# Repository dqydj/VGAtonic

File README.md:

VGAtonic
========

4 MBit Video Card supporting up to 640x480 resolution and 8 bit color depth over SPI.  Outputs to any standard VGA Monitor.

**What it is:**

VGAtonic is a video card for adding graphics output to computers, microcontrollers, and devices with SPI output.  It can generally support 5v, 3.3v and 2.5v SPI without level conversion, and can accept SPI of up to 60 MHz (or higher), giving 24.4 FPS as a worst case top speed for it's highest resolution and color depth.  It is also an entry to the [2015](https://hackaday.io/project/6309-vga-graphics-card-vgatonic) and [2014](https://hackaday.io/project/1943-vgatonic) Hackaday Prize competitions.

It additionally has hardware supported accelerations for various things, meaning that slower SPI links can still have useful display output:

 - 640x480 resolution  
 - 320x240 resolution
 - 160x120 resolution
 - 80x60 resolution
 - 8 bit color (256 colors)
 - 4 bit color (16 colors)
 - 2 bit color (4 colors)
 - 1 bit color (black & white)

Last, it also *accelerates screen positioning*, so the entire framebuffer need not be updated for a single refresh (allowing, for example, a menubar at the bottom of the screen to be updated at the full 60 Hz possible in the 640x480 resolution mode).

Importantly, all of these accelerations stack, so if you have a 4 MHz link, you can choose to target, say, 160x120x4 bits for 52 FPS worst case.

**How it's made:**

See the entire parts list in [this Hackaday Prize post](https://hackaday.io/project/6309-spi-and-ttl-serial-vga-graphics-card-vgatonic/log/21984-updated-bill-of-materials).  As part of the project, to keep it *interesting* (and keep costs down) I used modestly spec'd parts - a 144 Macrocell Xilinx XC95144XL CPLD instead of a large FPGA, and an 8 bit 128-Bytes of RAM Atmel ATTiny 2313a Microcontroller instead of one of the larger Atmel parts or something 32-bit (it's not even the largest part in its footprint).  Additionally, the pixel clock is provided by Linear Technology's LTC6903, allowing it to be changed on the fly (and, undoubtedly, tuned for specific monitors) by the microcontroller.  

You can find the schematics in the Rev A directory..

As for the software:

 - KiCad for the layout and Schematic
 - VHDL on Xilinx's ISE Webpack for the CPLD
 - C/C++ for any Microcontroller and Computer glue
 - C for the kernel code for the VGATonic Linux framebuffer drivers
 - Python where necessary

**How it's licensed:**

MIT (Hardware, Firmware, Python Examples, Arduino Code)  

GPL (Linux Framebuffer Drivers, Linux Userspace Code)  

LGPL (Changes to Arduino-Tiny Core)

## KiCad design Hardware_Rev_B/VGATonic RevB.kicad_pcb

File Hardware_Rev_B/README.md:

**NOTE:  This is the current version that should be built.  It has the NTSC pins and almost the same number of GPIOs broken out as Rev A on the optional unpopulated header on the back.**

**For VGA, there is no contest - build Rev B.  You will get more serial speeds, better ground isolation, shielding on the SPI signals, and... LEDs!**

By default, you should try the REGULAR firmware, not the WIDESCREEN firmware.  640x480 at 60Hz is industry standard, so that's the fallback (and it allows 320x240, 160x120 and 80x60 resolutions too for your slower parts or when you want to drive VGATonic over serial).  Once your board is working, the WIDESCREEN firmware is *much* nicer, but it only offers 848x480 and 424x240 resolutions.  It is only tested on rev B, but it likely works on rev A - just be careful.  Note, too, that the TERMINAL EMULATOR only works with the REGULAR firmware, it isn't yet updated for WIDESCREEN.

In this directory you'll find the design documentation for VGAtonic's second design, which we're naming v1.25 or "Rev B".  It is 39% smaller than the first version and contains 54 components (counting the headers and a single component each).

Returning are the Xilinx XC95144 CPLD, the ISSI IS61LV5128AL Memory, and the Linear LTC6903.

We've switched the Atmel 2313a up with the Atmel ATTiny 4313 (it's pin compatible), and clocked it with a 7.3728 MHz crystal which gives us magic frequencies to support lots of new serial speeds.  An external clock also saves us the optional calibration step in programming, which could be a bit of a hassle - now we'll have just two steps for the microcontroller, burning EEPROM then programming the rest.

Oh, we also added LEDs!  That, of course, is the best new feature.

License: MIT (see root directory)

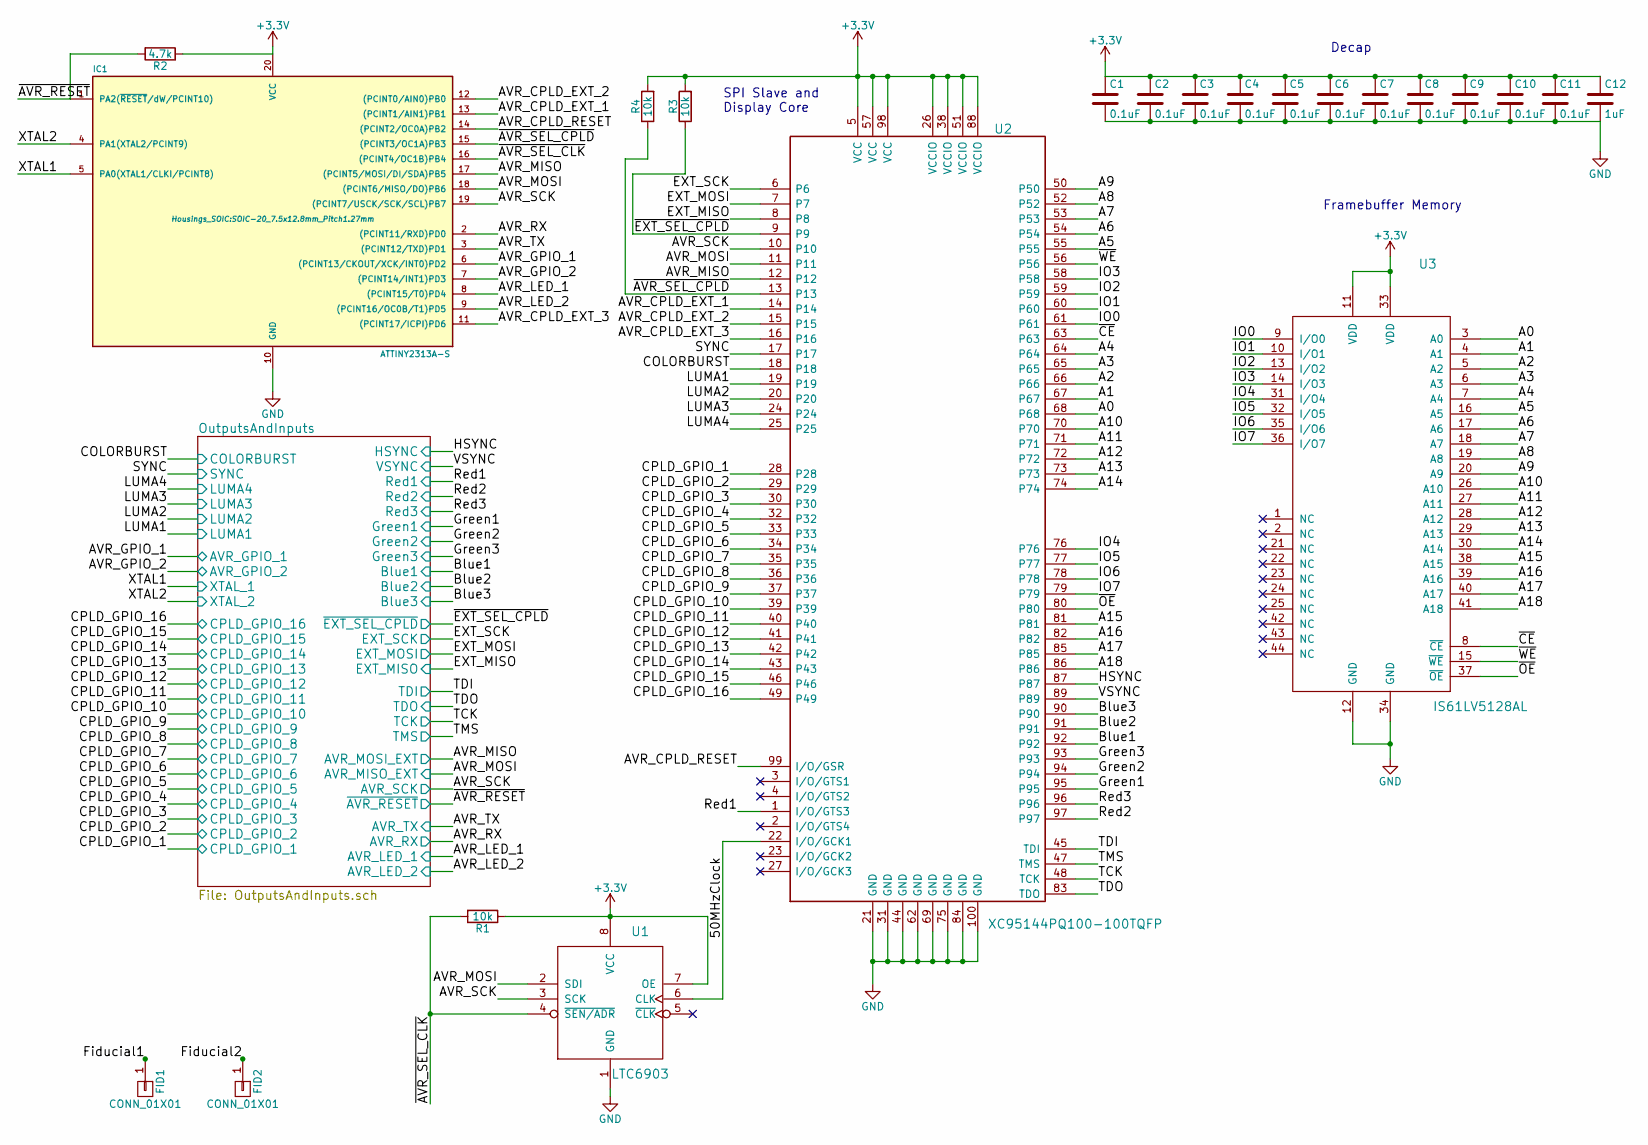
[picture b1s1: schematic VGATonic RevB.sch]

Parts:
C1, C2, C3, C4, C5, C6, C7, C8, C9, C10, C11: 0.1uF; C_0603
C12: 1uF; C_0603
FID1, FID2: CONN_01X01; Fiducial_1mm_Dia_2.54mm_Outer_CopperTop
IC1: ATTINY2313A-S; SOIC-20_7.5x12.8mm_Pitch1.27mm
R1, R3, R4: 10k; R_0805
R2: 4.7k; R_0805
U1: LTC6903; MSOP-8_3x3mm_Pitch0.65mm
U2: XC95144PQ100-100TQFP; TQFP-100_14x14mm_Pitch0.5mm
U3: IS61LV5128AL; tsop2-44

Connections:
+3V3: C1.1, C2.1, C3.1, C4.1, C5.1, C6.1, C7.1, C8.1, C9.1, C10.1, C11.1, C12.1, IC1.20 (VCC), R1.1, R2.1, R3.2, R4.2, U1.7 (OE), U1.8 (VCC), U2.5 (VCC), U2.26 (VCCIO), U2.38 (VCCIO), U2.51 (VCCIO), U2.57 (VCC), U2.88 (VCCIO), U2.98 (VCC), U3.11 (VDD), U3.33 (VDD); also elsewhere on the board
/50MHzClock: U1.6 (CLK), U2.22 (I/O/GCK1)
/A0: U2.68, U3.3 (A0)
/A1: U2.67, U3.4 (A1)
/A2: U2.66, U3.5 (A2)
/A3: U2.65, U3.6 (A3)
/A4: U2.64, U3.7 (A4)
/A5: U2.55, U3.16 (A5)
/A6: U2.54, U3.17 (A6)
/A7: U2.53, U3.18 (A7)
/A8: U2.52, U3.19 (A8)
/A9: U2.50, U3.20 (A9)
/A10: U2.70, U3.26 (A10)
/A11: U2.71, U3.27 (A11)
/A12: U2.72, U3.28 (A12)
/A13: U2.73, U3.29 (A13)
/A14: U2.74, U3.30 (A14)
/A15: U2.81, U3.38 (A15)
/A16: U2.82, U3.39 (A16)
/A17: U2.85, U3.40 (A17)
/A18: U2.86, U3.41 (A18)
/AVR_CPLD_EXT_1: IC1.13 ((PCINT1/AIN1)PB1), U2.14
/AVR_CPLD_EXT_2: IC1.12 ((PCINT0/AIN0)PB0), U2.15
/AVR_CPLD_EXT_3: IC1.11 ((PCINT17/ICPI)PD6), U2.16
/AVR_CPLD_RESET: IC1.14 ((PCINT2/OC0A)PB2), U2.99 (I/O/GSR)
/IO0: U2.61, U3.9 (I/O0)
/IO1: U2.60, U3.10 (I/O1)
/IO2: U2.59, U3.13 (I/O2)
/IO3: U2.58, U3.14 (I/O3)
/IO4: U2.76, U3.31 (I/O4)
/IO5: U2.77, U3.32 (I/O5)
/IO6: U2.78, U3.35 (I/O6)
/IO7: U2.79, U3.36 (I/O7)
/OutputsAndInputs/AVR_GPIO_1: IC1.6 ((PCINT13/CKOUT/XCK/INT0)PD2); also elsewhere on the board
/OutputsAndInputs/AVR_GPIO_2: IC1.7 ((PCINT14/INT1)PD3); also elsewhere on the board
/OutputsAndInputs/AVR_LED_1: IC1.8 ((PCINT15/T0)PD4); also elsewhere on the board
/OutputsAndInputs/AVR_LED_2: IC1.9 ((PCINT16/OC0B/T1)PD5); also elsewhere on the board
/OutputsAndInputs/AVR_MISO_EXT: IC1.18 ((PCINT6/MISO/DO)PB6), U1.2 (SDI), U2.11; also elsewhere on the board
/OutputsAndInputs/AVR_MOSI_EXT: IC1.17 ((PCINT5/MOSI/DI/SDA)PB5), U2.12; also elsewhere on the board
/OutputsAndInputs/AVR_RX: IC1.2 ((PCINT11/RXD)PD0); also elsewhere on the board
/OutputsAndInputs/AVR_SCK: IC1.19 ((PCINT7/USCK/SCK/SCL)PB7), U1.3 (SCK), U2.10; also elsewhere on the board
/OutputsAndInputs/AVR_TX: IC1.3 ((PCINT12/TXD)PD1); also elsewhere on the board
/OutputsAndInputs/Blue1: U2.92; also elsewhere on the board
/OutputsAndInputs/Blue2: U2.91; also elsewhere on the board
/OutputsAndInputs/Blue3: U2.90; also elsewhere on the board
/OutputsAndInputs/COLORBURST: U2.18; also elsewhere on the board
/OutputsAndInputs/CPLD_GPIO_1: U2.28; also elsewhere on the board
/OutputsAndInputs/CPLD_GPIO_2: U2.29; also elsewhere on the board
/OutputsAndInputs/CPLD_GPIO_3: U2.30; also elsewhere on the board
/OutputsAndInputs/CPLD_GPIO_4: U2.32; also elsewhere on the board
/OutputsAndInputs/CPLD_GPIO_5: U2.33; also elsewhere on the board
/OutputsAndInputs/CPLD_GPIO_6: U2.34; also elsewhere on the board
/OutputsAndInputs/CPLD_GPIO_7: U2.35; also elsewhere on the board
/OutputsAndInputs/CPLD_GPIO_8: U2.36; also elsewhere on the board
/OutputsAndInputs/CPLD_GPIO_9: U2.37; also elsewhere on the board
/OutputsAndInputs/CPLD_GPIO_10: U2.39; also elsewhere on the board
/OutputsAndInputs/CPLD_GPIO_11: U2.40; also elsewhere on the board
/OutputsAndInputs/CPLD_GPIO_12: U2.41; also elsewhere on the board
/OutputsAndInputs/CPLD_GPIO_13: U2.42; also elsewhere on the board
/OutputsAndInputs/CPLD_GPIO_14: U2.43; also elsewhere on the board
/OutputsAndInputs/CPLD_GPIO_15: U2.46; also elsewhere on the board
/OutputsAndInputs/CPLD_GPIO_16: U2.49; also elsewhere on the board
/OutputsAndInputs/EXT_MISO: U2.8; also elsewhere on the board
/OutputsAndInputs/EXT_MOSI: U2.7; also elsewhere on the board
/OutputsAndInputs/EXT_SCK: U2.6; also elsewhere on the board
/OutputsAndInputs/Green1: U2.95; also elsewhere on the board
/OutputsAndInputs/Green2: U2.94; also elsewhere on the board
/OutputsAndInputs/Green3: U2.93; also elsewhere on the board
/OutputsAndInputs/HSYNC: U2.87; also elsewhere on the board
/OutputsAndInputs/LUMA1: U2.19; also elsewhere on the board
/OutputsAndInputs/LUMA2: U2.20; also elsewhere on the board
/OutputsAndInputs/LUMA3: U2.24; also elsewhere on the board
/OutputsAndInputs/LUMA4: U2.25; also elsewhere on the board
/OutputsAndInputs/Red1: U2.1 (I/O/GTS3); also elsewhere on the board
/OutputsAndInputs/Red2: U2.97; also elsewhere on the board
/OutputsAndInputs/Red3: U2.96; also elsewhere on the board
/OutputsAndInputs/SYNC: U2.17; also elsewhere on the board
/OutputsAndInputs/TCK: U2.48 (TCK); also elsewhere on the board
/OutputsAndInputs/TDI: U2.45 (TDI); also elsewhere on the board
/OutputsAndInputs/TDO: U2.83 (TDO); also elsewhere on the board
/OutputsAndInputs/TMS: U2.47 (TMS); also elsewhere on the board
/OutputsAndInputs/VSYNC: U2.89; also elsewhere on the board
/OutputsAndInputs/XTAL_1: IC1.5 (PA0(XTAL1/CLKI/PCINT8)); also elsewhere on the board
/OutputsAndInputs/XTAL_2: IC1.4 (PA1(XTAL2/PCINT9)); also elsewhere on the board
/OutputsAndInputs/~AVR_RESET: IC1.1 (PA2(~RESET~/dW/PCINT10)), R2.2; also elsewhere on the board
/OutputsAndInputs/~EXT_SEL_CPLD: R3.1, U2.9; also elsewhere on the board
/~AVR_SEL_CLK: IC1.16 ((PCINT4/OC1B)PB4), R1.2, U1.4 (~SEN/ADR)
/~AVR_SEL_CPLD: IC1.15 ((PCINT3/OC1A)PB3), R4.1, U2.13
/~CE: U2.63, U3.8 (~CE)
/~OE: U2.80, U3.37 (~OE)
/~WE: U2.56, U3.15 (~WE)
GND: C1.2, C2.2, C3.2, C4.2, C5.2, C6.2, C7.2, C8.2, C9.2, C10.2, C11.2, C12.2, IC1.10 (GND), U1.1 (GND), U2.21 (GND), U2.31 (GND), U2.44 (GND), U2.62 (GND), U2.69 (GND), U2.75 (GND), U2.84 (GND), U2.100 (GND), U3.12 (GND), U3.34 (GND); also elsewhere on the board

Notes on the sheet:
Decap
Framebuffer Memory
SPI Slave and Display Core

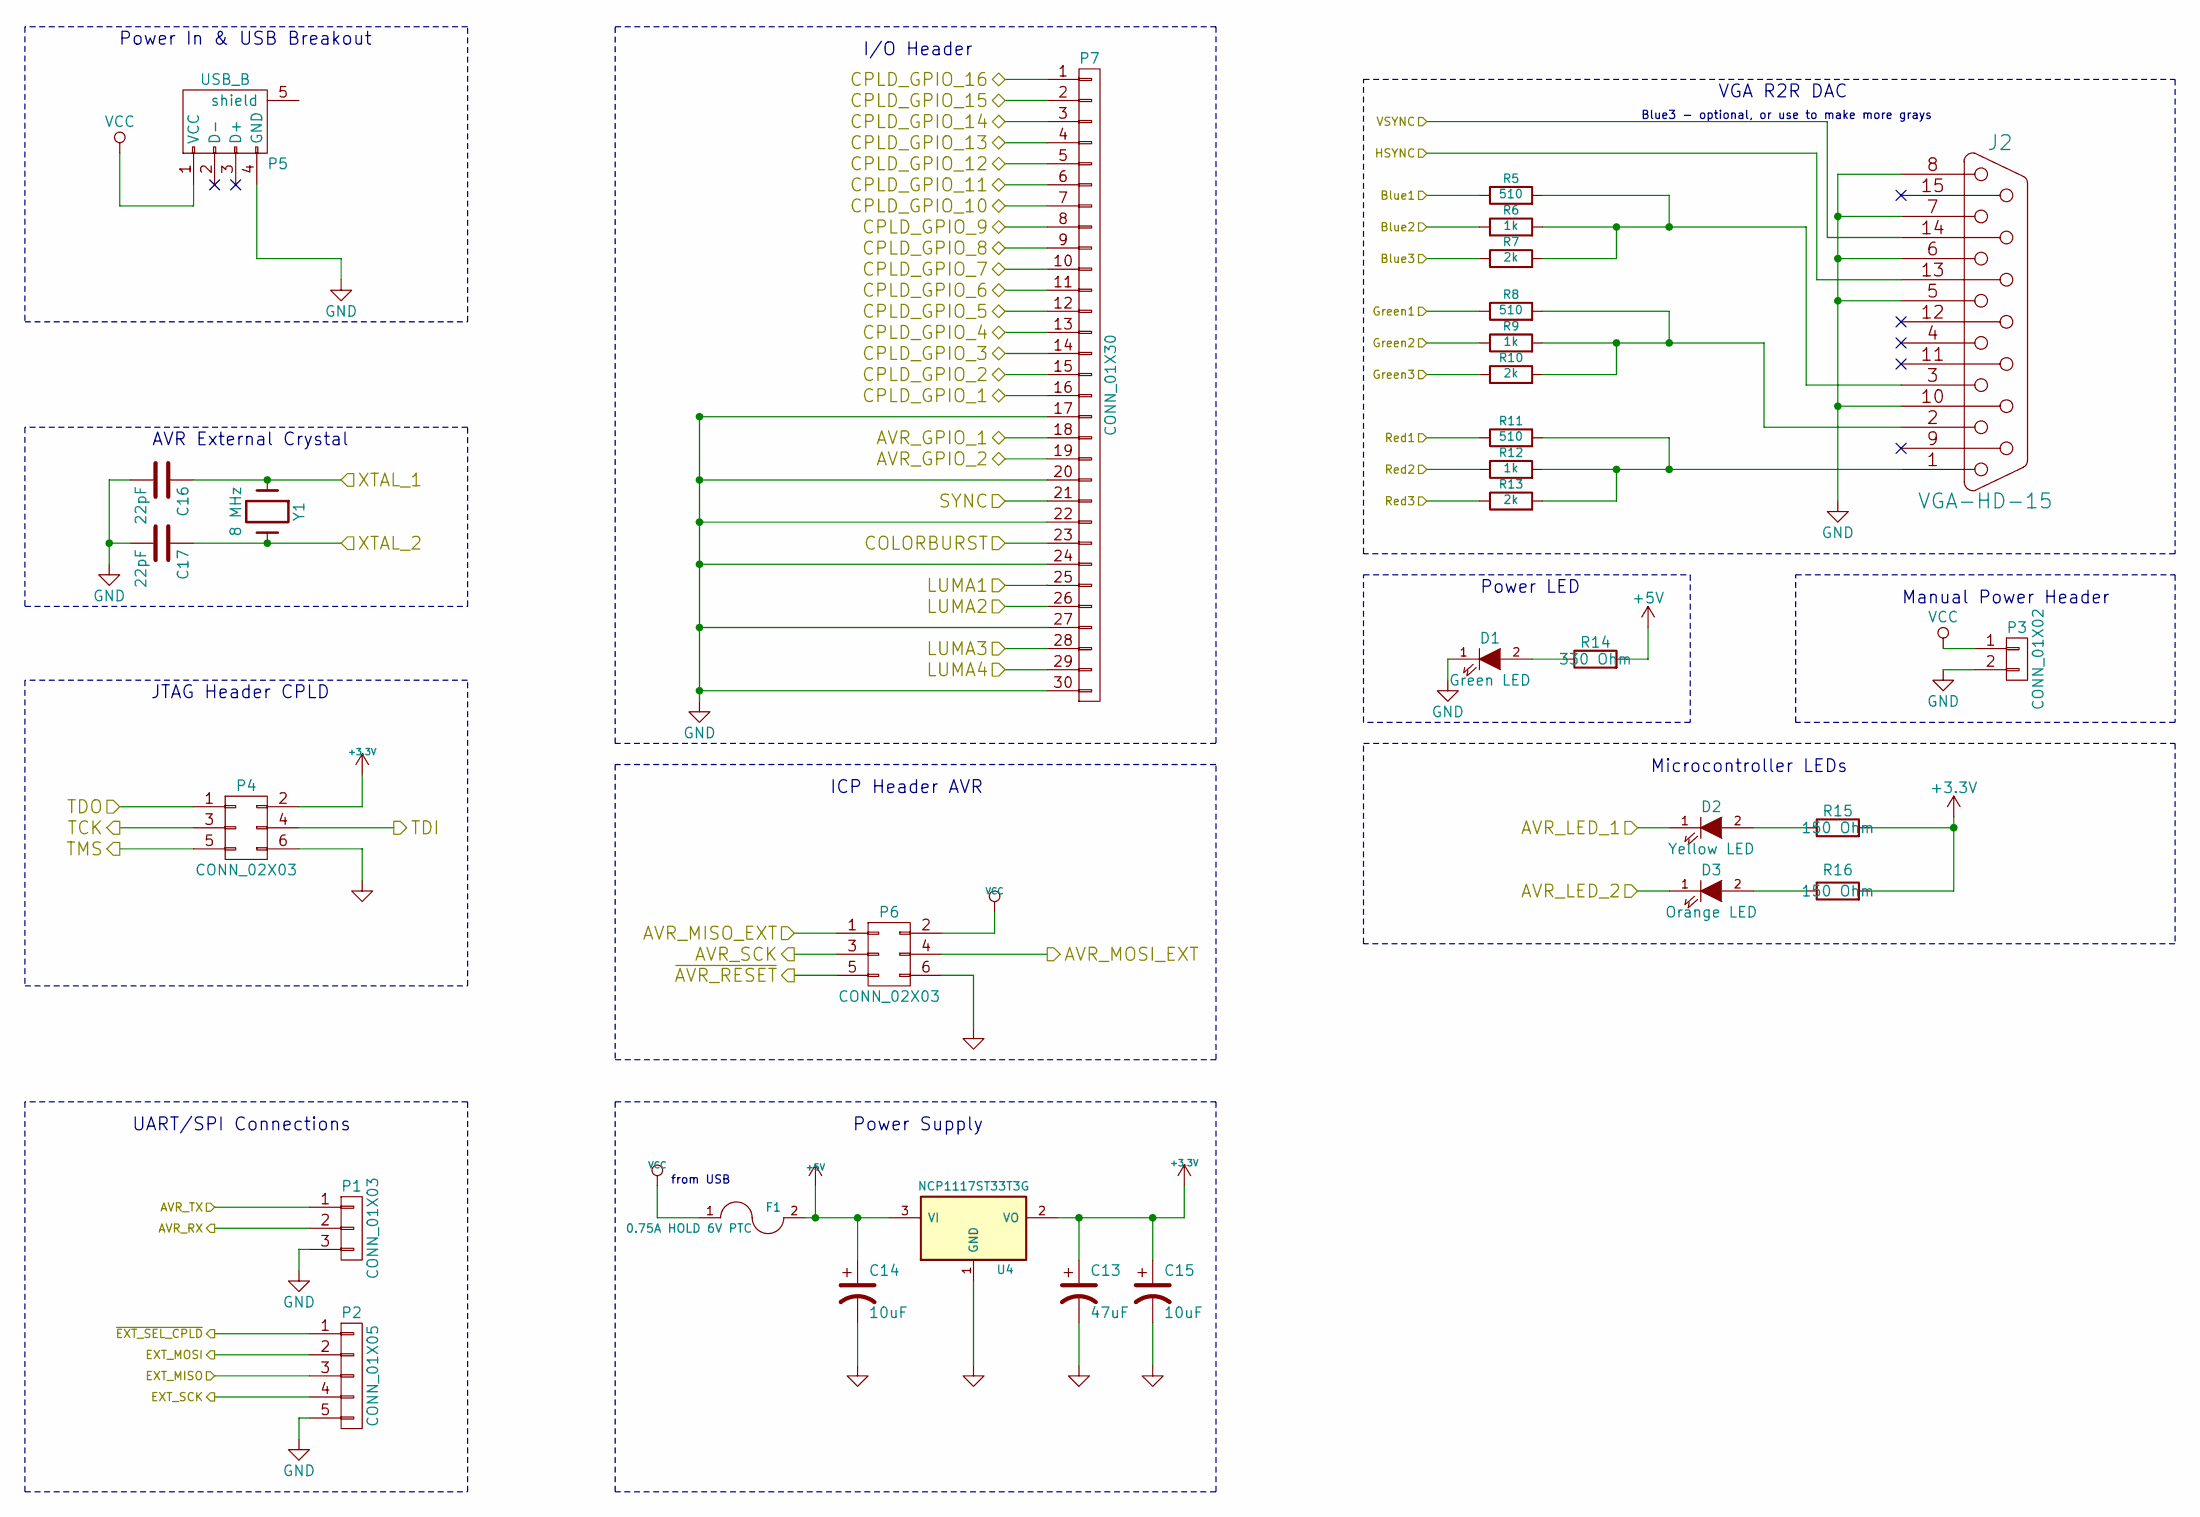
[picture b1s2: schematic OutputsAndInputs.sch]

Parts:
C13: 47uF; SMD-1206_Pol
C14, C15: 10uF; SMD-1206_Pol
C16, C17: 22pF; C_0603
D1: Green LED; LED-0603
D2: Yellow LED; LED-0603
D3: Orange LED; LED-0603
F1: 0.75A HOLD 6V PTC; R_1210
J2: VGA-HD-15; HD15_B-HD15F
P1: CONN_01X03; Pin_Header_Straight_1x03
P2: CONN_01X05; Pin_Header_Straight_1x05
P3: CONN_01X02; Pin_Header_Straight_1x02
P4, P6: CONN_02X03; Pin_Header_Straight_2x03
P5: USB_B
P7: CONN_01X30; DF40C-30DS-0.4V
R5, R8, R11: 510; R_0805
R6, R9, R12: 1k; R_0805
R7, R10, R13: 2k; R_0805
R14: 330 Ohm; R_0805
R15, R16: 150 Ohm; R_0805
U4: NCP1117ST33T3G; SOT223_PWR
Y1: 8 MHz; HC49_sm

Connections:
+3V3: C13.1, C15.1, P4.2, R15.2, R16.2, U4.2 (VO); also elsewhere on the board
+5V: C14.1, F1.2, R14.2, U4.3 (VI)
/OutputsAndInputs/AVR_GPIO_1: P7.18; also elsewhere on the board
/OutputsAndInputs/AVR_GPIO_2: P7.19; also elsewhere on the board
/OutputsAndInputs/AVR_LED_1: D2.1 (K); also elsewhere on the board
/OutputsAndInputs/AVR_LED_2: D3.1 (K); also elsewhere on the board
/OutputsAndInputs/AVR_MISO_EXT: P6.1; also elsewhere on the board
/OutputsAndInputs/AVR_MOSI_EXT: P6.4; also elsewhere on the board
/OutputsAndInputs/AVR_RX: P1.2; also elsewhere on the board
/OutputsAndInputs/AVR_SCK: P6.3; also elsewhere on the board
/OutputsAndInputs/AVR_TX: P1.1; also elsewhere on the board
/OutputsAndInputs/Blue1: R5.1; also elsewhere on the board
/OutputsAndInputs/Blue2: R6.1; also elsewhere on the board
/OutputsAndInputs/Blue3: R7.1; also elsewhere on the board
/OutputsAndInputs/COLORBURST: P7.23; also elsewhere on the board
/OutputsAndInputs/CPLD_GPIO_1: P7.16; also elsewhere on the board
/OutputsAndInputs/CPLD_GPIO_2: P7.15; also elsewhere on the board
/OutputsAndInputs/CPLD_GPIO_3: P7.14; also elsewhere on the board
/OutputsAndInputs/CPLD_GPIO_4: P7.13; also elsewhere on the board
/OutputsAndInputs/CPLD_GPIO_5: P7.12; also elsewhere on the board
/OutputsAndInputs/CPLD_GPIO_6: P7.11; also elsewhere on the board
/OutputsAndInputs/CPLD_GPIO_7: P7.10; also elsewhere on the board
/OutputsAndInputs/CPLD_GPIO_8: P7.9; also elsewhere on the board
/OutputsAndInputs/CPLD_GPIO_9: P7.8; also elsewhere on the board
/OutputsAndInputs/CPLD_GPIO_10: P7.7; also elsewhere on the board
/OutputsAndInputs/CPLD_GPIO_11: P7.6; also elsewhere on the board
/OutputsAndInputs/CPLD_GPIO_12: P7.5; also elsewhere on the board
/OutputsAndInputs/CPLD_GPIO_13: P7.4; also elsewhere on the board
/OutputsAndInputs/CPLD_GPIO_14: P7.3; also elsewhere on the board
/OutputsAndInputs/CPLD_GPIO_15: P7.2; also elsewhere on the board
/OutputsAndInputs/CPLD_GPIO_16: P7.1; also elsewhere on the board
/OutputsAndInputs/EXT_MISO: P2.3; also elsewhere on the board
/OutputsAndInputs/EXT_MOSI: P2.2; also elsewhere on the board
/OutputsAndInputs/EXT_SCK: P2.4; also elsewhere on the board
/OutputsAndInputs/Green1: R8.1; also elsewhere on the board
/OutputsAndInputs/Green2: R9.1; also elsewhere on the board
/OutputsAndInputs/Green3: R10.1; also elsewhere on the board
/OutputsAndInputs/HSYNC: J2.13; also elsewhere on the board
/OutputsAndInputs/LUMA1: P7.25; also elsewhere on the board
/OutputsAndInputs/LUMA2: P7.26; also elsewhere on the board
/OutputsAndInputs/LUMA3: P7.28; also elsewhere on the board
/OutputsAndInputs/LUMA4: P7.29; also elsewhere on the board
/OutputsAndInputs/Red1: R11.1; also elsewhere on the board
/OutputsAndInputs/Red2: R12.1; also elsewhere on the board
/OutputsAndInputs/Red3: R13.1; also elsewhere on the board
/OutputsAndInputs/SYNC: P7.21; also elsewhere on the board
/OutputsAndInputs/TCK: P4.3; also elsewhere on the board
/OutputsAndInputs/TDI: P4.4; also elsewhere on the board
/OutputsAndInputs/TDO: P4.1; also elsewhere on the board
/OutputsAndInputs/TMS: P4.5; also elsewhere on the board
/OutputsAndInputs/VSYNC: J2.14; also elsewhere on the board
/OutputsAndInputs/XTAL_1: C16.1, Y1.1; also elsewhere on the board
/OutputsAndInputs/XTAL_2: C17.1, Y1.2; also elsewhere on the board
/OutputsAndInputs/~AVR_RESET: P6.5; also elsewhere on the board
/OutputsAndInputs/~EXT_SEL_CPLD: P2.1; also elsewhere on the board
GND: C13.2, C14.2, C15.2, C16.2, C17.2, D1.1 (K), J2.5, J2.6, J2.7, J2.8, J2.10, P1.3, P2.5, P3.2, P4.6, P5.4 (GND), P6.6, P7.17, P7.20, P7.22, P7.24, P7.27, P7.30, U4.1 (GND); also elsewhere on the board
unnamed: D1.2 (A), R14.1
unnamed: D2.2 (A), R15.1
unnamed: D3.2 (A), R16.1
unnamed: J2.1, R11.2, R12.2, R13.2
unnamed: J2.2, R8.2, R9.2, R10.2
unnamed: J2.3, R5.2, R6.2, R7.2
VCC: F1.1, P3.1, P5.1 (VCC), P6.2

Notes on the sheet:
VGA R2R DAC
Blue3 - optional, or use to make more grays
Power In & USB Breakout
JTAG Header CPLD
ICP Header AVR
I/O Header
Power Supply
from USB
UART/SPI Connections
AVR External Crystal
Manual Power Header
Power LED
Microcontroller LEDs

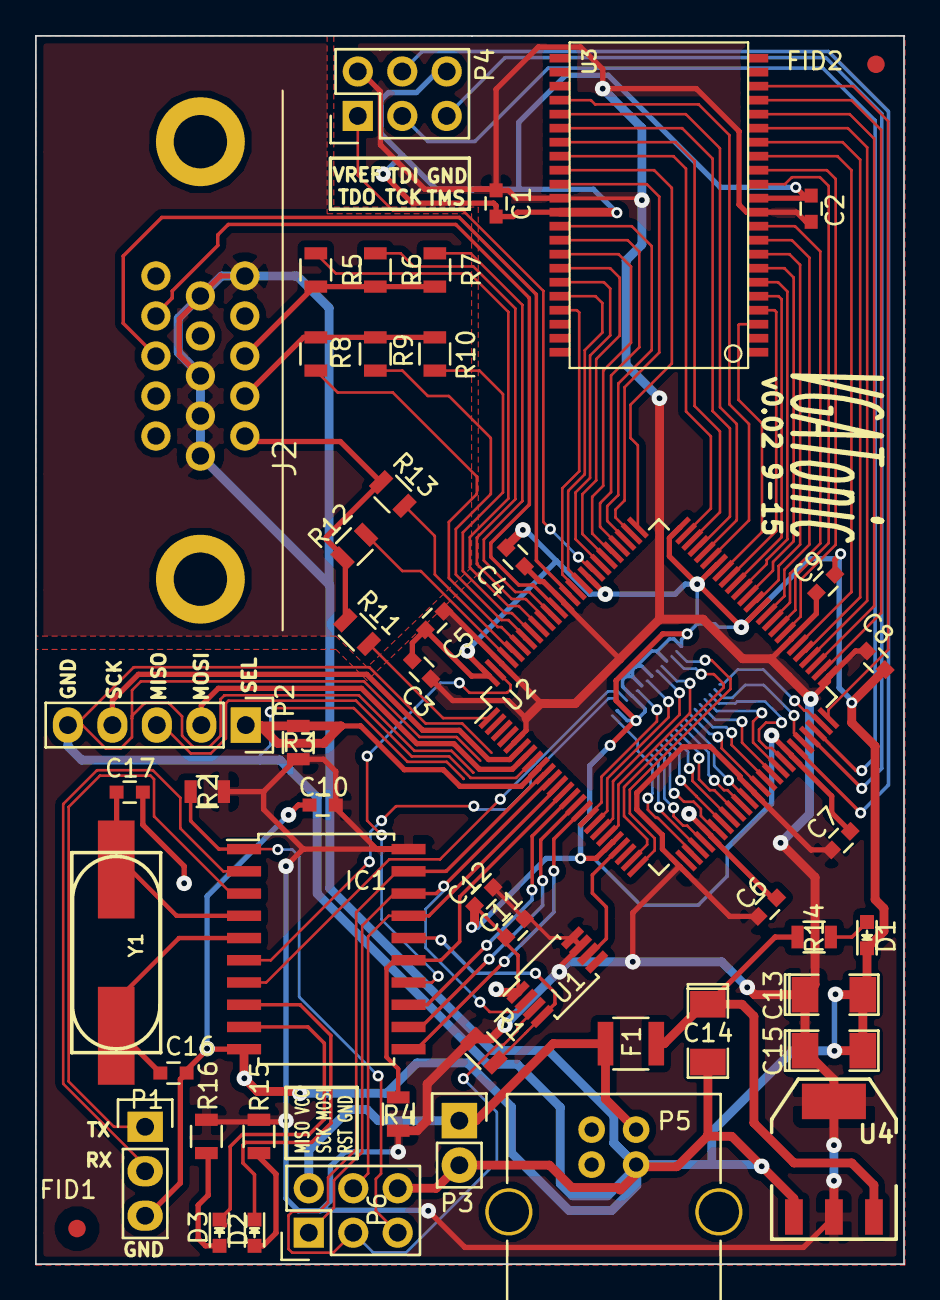
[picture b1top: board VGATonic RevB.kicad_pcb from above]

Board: 2 copper layers, 49.6 x 70.2 mm, 53 parts (1 on the bottom side), 100 nets.

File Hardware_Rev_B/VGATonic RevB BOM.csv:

Reference	 Value	 Footprint	Cost / Board	Supplier	Quantity Required	Notes
IC1	ATTINY4313	Housings_SOIC:SOIC-20_7.5x12.8mm_Pitch1.27mm	1.59	Newark	1	
C1	0.1uF	Capacitors_SMD:C_0603	0.00359	Digikey	4000	X7R
C2	0.1uF	Capacitors_SMD:C_0603	0.00359	Digikey	4000	X7R
C3	0.1uF	Capacitors_SMD:C_0603	0.00359	Digikey	4000	X7R
C4	0.1uF	Capacitors_SMD:C_0603	0.00359	Digikey	4000	X7R
C5	0.1uF	Capacitors_SMD:C_0603	0.00359	Digikey	4000	X7R
C6	0.1uF	Capacitors_SMD:C_0603	0.00359	Digikey	4000	X7R
C7	0.1uF	Capacitors_SMD:C_0603	0.00359	Digikey	4000	X7R
C8	0.1uF	Capacitors_SMD:C_0603	0.00359	Digikey	4000	X7R
C9	0.1uF	Capacitors_SMD:C_0603	0.00359	Digikey	4000	X7R
C10	0.1uF	Capacitors_SMD:C_0603	0.00359	Digikey	4000	X7R
C11	0.1uF	Capacitors_SMD:C_0603	0.00359	Digikey	4000	X7R
C12	1uF	Capacitors_SMD:C_0603	0.1	Digikey	1	X7R
U3	IS61LV5128AL	Footprints:tsop2-44	4.85	Jameco	1	
U1	LTC6903	Housings_SSOP:MSOP-8_3x3mm_Pitch0.65mm	3.92	Digikey	1	
U2	XC95144PQ100-100TQFP	Housings_QFP:TQFP-100_14x14mm_Pitch0.5mm	7.25	Digikey	1	
R2	4.7k	Resistors_SMD:R_0805	0.018	Digikey	10	5.00%
R1	10k	Resistors_SMD:R_0805	0.018	Digikey	10	5.00%
R3	10k	Resistors_SMD:R_0805	0.018	Digikey	10	5.00%
R4	10k	Resistors_SMD:R_0805	0.018	Digikey	10	5.00%
FID1	CONN_01X01	Fiducials:Fiducial_1mm_Dia_2.54mm_Outer_CopperTop	0			5.00%
FID2	CONN_01X01	Fiducials:Fiducial_1mm_Dia_2.54mm_Outer_CopperTop	0			5.00%
R11	510	Resistors_SMD:R_0805	0.021	Digikey	10	1.00%
R12	1k	Resistors_SMD:R_0805	0.021	Digikey	10	1.00%
R13	2k	Resistors_SMD:R_0805	0.021	Digikey	10	1.00%
R8	510	Resistors_SMD:R_0805	0.021	Digikey	10	1.00%
R9	1k	Resistors_SMD:R_0805	0.021	Digikey	10	1.00%
R10	2k	Resistors_SMD:R_0805	0.021	Digikey	10	1.00%
R5	510	Resistors_SMD:R_0805	0.021	Digikey	10	1.00%
R6	1k	Resistors_SMD:R_0805	0.021	Digikey	10	1.00%
R7	2k	Resistors_SMD:R_0805	0.021	Digikey	10	1.00%
F1	0.75A HOLD 6V PTC	Resistors_SMD:R_1210	0.2544	Newark	10	
U4	NCP1117ST33T3G	Footprints:SOT223_PWR	0.49	Digikey	1	LDO Not Needed
C14	10uF	SMD_Packages:SMD-1206_Pol	0.4848	Newark	5	Tantalum, 6.3V
C15	10uF	SMD_Packages:SMD-1206_Pol	0.4848	Newark	5	Tantalum, 6.3V
C13	47uF	SMD_Packages:SMD-1206_Pol	0.0672	Newark	1	Tantalum, 6.3V
P6	CONN_02X03	Pin_Headers:Pin_Header_Straight_2x03	0.06			
J2	VGA-HD-15	Footprints:HD15_B-HD15F	1.18	Newark	1	Newark 54M6031
C16	22pF	Capacitors_SMD:C_0603	0.024	Digikey	10	X7R
C17	22pF	Capacitors_SMD:C_0603	0.024	Digikey	10	X7R
Y1	7.3728 MHz	crystal:HC49_sm	0.325	eBay	20	MFG Not Important
P1	CONN_01X03	Pin_Headers:Pin_Header_Straight_1x03	0.03			
P2	CONN_01X05	Pin_Headers:Pin_Header_Straight_1x05	0.05			
P3	CONN_01X02	Pin_Headers:Pin_Header_Straight_1x02	0.02			
P4	CONN_02X03	Pin_Headers:Pin_Header_Straight_2x03	0.06			
P7	CONN_01X30	Footprints:DF40C-30DS-0.4V				Optional 
D1	Green LED	LEDs:LED-0603	0.0495	Jameco		You Pick Color
R14	330 Ohm	Resistors_SMD:R_0805	0.212	Digikey		5.00%
R15	150 Ohm	Resistors_SMD:R_0805	0.212	Digikey		5.00%
R16	150 Ohm	Resistors_SMD:R_0805	0.194	Digikey		5.00%
D2	Yellow LED	LEDs:LED-0603	0.0495	Jameco		You Pick Color
D3	Orange LED	LEDs:LED-0603	0.0495	Jameco		You Pick Color
P5	USB_B	Connect:USB_B	0.5528	Newark		Newark 14N8154
			22.88399

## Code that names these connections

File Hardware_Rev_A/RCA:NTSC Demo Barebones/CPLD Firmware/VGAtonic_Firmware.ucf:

NET "CLK" LOC = "P22"; 			# Input from LTC693 Programmable Oscillator


// Outside World SPI Interface
NET "EXT_SCK" 			LOC = "P6";
NET "EXT_MOSI" 		LOC = "P7";
NET "EXT_MISO" 		LOC = "P8";
NET "EXT_SEL_CPLD" 	LOC = "P9";

// Outside World SPI Interface
NET "AVR_SCK" 			LOC = "P10";
NET "AVR_MOSI" 		LOC = "P11";
//NET "AVR_MISO" 		LOC = "P12";
//NET "AVR_SEL_CPLD" 	LOC = "P13";
// Control Signal to Ignore Outside SPI - Switch 1
//NET "SW_1" 				LOC = "P2";
NET "AVR_CPLD_EXT_1"	LOC = "P14";
NET "AVR_CPLD_EXT_2"	LOC = "P15";

// VGA Interface
//NET "Pixel<8>"			LOC = "P1"; // Red MSB
//NET "Pixel<7>"			LOC = "P97"; // Red Middle
//NET "Pixel<6>"			LOC = "P96"; // Red LSB

//NET "Pixel<5>"			LOC = "P95"; // Green MSB
//NET "Pixel<4>"			LOC = "P94"; // Green Middle
//NET "Pixel<3>"			LOC = "P93"; // Green LSB

//NET "Pixel<2>"			LOC = "P92"; // Blue MSB
//NET "Pixel<1>"			LOC = "P91"; // Blue Middle
//NET "Pixel<0>"			LOC = "P90"; // Blue LSB - Optional; needed for true greys

//NET "VSYNC"				LOC = "P89"; // Vertical Sync Signal
//NET "HSYNC"				LOC = "P87"; // Vertical Sync Signal

// NTSC Interface
// SWAPPED COLORBURST AND SYNC FROM SCHEMATIC
//NET "SYNC"				LOC = "P17";
NET "COLORBURST"		LOC = "P18";
NET "SYNC"				LOC = "P19";



NET "LUMA<3>"			LOC = "P20";
NET "LUMA<2>"			LOC = "P17";
NET "LUMA<1>"			LOC = "P24";
NET "LUMA<0>"			LOC = "P25";

// Memory - Addresses, Data, Control Signals

NET "WE_LOW"			LOC = "P56"; // Write enable, active low
NET "CE_LOW"			LOC = "P63"; // Chip enable, active low
NET "OE_LOW"			LOC = "P80"; // Output enable, active low

NET "ADDR<0>"			LOC = "P68";
NET "ADDR<1>"			LOC = "P67";
NET "ADDR<2>"			LOC = "P66";
NET "ADDR<3>"			LOC = "P65";
NET "ADDR<4>"			LOC = "P64";
NET "ADDR<5>"			LOC = "P55";
NET "ADDR<6>"			LOC = "P54";
NET "ADDR<7>"			LOC = "P53";
NET "ADDR<8>"			LOC = "P52";
NET "ADDR<9>"			LOC = "P50";
NET "ADDR<10>"			LOC = "P70";
NET "ADDR<11>"			LOC = "P71";
NET "ADDR<12>"			LOC = "P72";
NET "ADDR<13>"			LOC = "P73";
NET "ADDR<14>"			LOC = "P74";
NET "ADDR<15>"			LOC = "P81";
NET "ADDR<16>"			LOC = "P82";
NET "ADDR<17>"			LOC = "P85";
NET "ADDR<18>"			LOC = "P86";

NET "DATA<0>"			LOC = "P61";
NET "DATA<1>"			LOC = "P60";
NET "DATA<2>"			LOC = "P59";
NET "DATA<3>"			LOC = "P58";
NET "DATA<4>"			LOC = "P76";
NET "DATA<5>"			LOC = "P77";
NET "DATA<6>"			LOC = "P78";
NET "DATA<7>"			LOC = "P79";

// GPIO Header, Bottom of Board
//NET "CPLD_GPIO<1>" LOC = "P28"; 		# CPLD GPIO 1
//NET "CPLD_GPIO<2>" LOC = "P29"; 		# CPLD GPIO 2
//NET "CPLD_GPIO<3>" LOC = "P30"; 		# CPLD GPIO 3
//NET "CPLD_GPIO<4>" LOC = "P32"; 		# CPLD GPIO 4
//NET "CPLD_GPIO<5>" LOC = "P33"; 		# CPLD GPIO 5
//NET "CPLD_GPIO<6>" LOC = "P34"; 		# CPLD GPIO 6
//NET "CPLD_GPIO<7>" LOC = "P35"; 		# CPLD GPIO 7
//NET "CPLD_GPIO<8>" LOC = "P36"; 		# CPLD GPIO 8
//NET "CPLD_GPIO<9>" LOC = "P37"; 		# CPLD GPIO 9
//NET "CPLD_GPIO<10>" LOC = "P39"; 		# CPLD GPIO 10
//NET "CPLD_GPIO<11>" LOC = "P40"; 		# CPLD GPIO 11
//NET "CPLD_GPIO<12>" LOC = "P41"; 		# CPLD GPIO 12
//NET "CPLD_GPIO<13>" LOC = "P42"; 		# CPLD GPIO 13
//NET "CPLD_GPIO<14>" LOC = "P43"; 		# CPLD GPIO 14
//NET "CPLD_GPIO<15>" LOC = "P46"; 		# CPLD GPIO 15
//NET "CPLD_GPIO" LOC = "P49"; 		# CPLD GPIO 16

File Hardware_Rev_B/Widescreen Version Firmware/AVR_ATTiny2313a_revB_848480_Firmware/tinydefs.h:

/* Definitions File for Tiny 2313a Firmware on VGATonic Board */

#ifndef TINYDEFS_H
#define TINYDEFS_H

// EEPROM Locations - Don't change it unless you also update the EEPROM!  Beware: only 128 bytes available.
#define OSCALSPEED   0
#define LTCSPEED     1
#define HELLOMSG     2  // Welcome string
#define FONTSTORAGE  21 // Where the MSBs of our font reside.  We write 95 bytes from here.

// Serial Constants - Wishlist: change speed.
//#define USART_BAUDRATE 38400
#define F_CPU 7372800UL
#define BAUD_PRESCALE(baudrate)     (((F_CPU / (baudrate * 16UL))) - 1)
#define BAUD_PRESCALE_U2X(baudrate) (((F_CPU / (baudrate * 8UL))) - 1)

// Macros to flip IOs
#define CPLD_LOW     PORTB  &= ~(1 << PB0)
#define CPLD_HIGH    PORTB  |=  (1 << PB0)
#define CLK_LOW      PORTB  &= ~(1 << PB4)
#define CLK_HIGH     PORTB  |=  (1 << PB4)

#define CPLD_GIVE    PORTB  &= ~(1 << PB1)
#define CPLD_TAKE    PORTB  |=  (1 << PB1)

#define SCK_LOW      PORTB  &= ~(1 << PB7)
#define SCK_HIGH     PORTB  |=  (1 << PB7)
#define DI_LOW       PORTB  &= ~(1 << PB5)
#define DI_HIGH      PORTB  |=  (1 << PB5)

// SPI Definitions
#define SCK_LOW      PORTB  &= ~(1 << PB7)
#define SCK_HIGH     PORTB  |= (1 << PB7)
#define DI_LOW       PORTB  &= ~(1 << PB5)
#define DI_HIGH      PORTB  |= (1 << PB5)

//UART Definitions
#define BUFFER_SIZE  128
#define TERMINAL_LINE_MAX 40
#define NO_DATA      0x0100
#define OFF_U2X      UCSRA &= ~(1 << U2X);
#define USE_U2X      UCSRA |= (1 << U2X);

// LED Definitions

#define LED1_ON      PORTD  &= ~(1 << PD4);
#define LED1_OFF     PORTD  |=  (1 << PD4)
#define LED2_ON      PORTD  &= ~(1 << PD5);
#define LED2_OFF     PORTD  |=  (1 << PD5)

#endif

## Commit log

2014-07-27 Create SPISlave.vhd
    SPI Slave exaple, with clock domain crossing to user logic.
2014-07-27 Create README.md
    Readme for the SPI Slave example.
2014-08-05 Create CPLD_ColorTest.vhd
    VGA and NTSC from a single 64 macrocell CPLD, with a single 3.5795454 MHz clock source.
2014-08-10 Adding reference and build documentation
2014-08-10 Update README.md
    Forgot a note on license.
2014-08-29 Adding the CPLD Firmware
2014-08-29 Create Howtouse.txt
    How to call VGAtonic with this firmware.
2014-08-30 ATTiny 2313a Firmware
2014-09-03 Adding userland code from Arduino
2014-09-03 Python script
2015-06-01 Userland driver for VGAtonic (based on RPi 2 B, but easily adaptable\!)
2015-06-01 .DS_Store banished\!
2015-06-01 Adding Framebuffer driver for Raspberry Pi 2 B
2015-06-01 Update Readme.md
    Beautifying
2015-06-08 Update Readme.md
    I guess I don't know markup. This will work equally as well.
2015-06-08 Raspberry Pi 62.5 MHz SPI because 58 MHz is nonsense (rounds to 31.25 MHz)
2015-06-15 Didn't see that Page 1 of the Schematic was impossible to see. So, making it easier to see with a new PDF of page 1.
2015-06-28 BPP and Resolution code
2015-07-07 'Finished' hardware code. HW acceleration, 4 accelerated resolutions, 4 accelerated bitdepths, allowing microcontroller writes (and master of bus).
2015-07-07 SPI Slave code with support for AVR writing SPI to VGATonic
2015-07-11 Caffeine update - tons of Microcontroller features. See README
2015-07-11 Readme with vt52 escape codes.
2015-07-13 Hardware accelerated lower resolutions
2015-07-13 Removing dubious file remnants
2015-07-13 Removing spurious temp directory
2015-07-13 Create Readme.md
    How to install/build
2015-07-18 Beaglebone Black support added to VGATonic
2015-07-18 Readme
2015-07-23 Terminal Codes
2015-07-29 Fixed DMA, Added Pseudo Color Bit (Always 16), Changed SPI Write Buffer to kmalloc from vzalloc, BBB working properly, Intel Edison Added.
2015-08-09 Build details
2015-08-12 Licenses more explicit, updating BBB frames per second to 19.25
2015-08-12 One more image
2015-08-14 Modification to LGPL arduino-tiny code
2015-08-16 Documentation
2015-08-16 Arduino driver, hardware acceleration
2015-08-16 UCF file behind local copy
2015-08-17 Update README.md
    License change, BOM.
2015-08-17 Cleanup for contest deadline
2015-09-07 Rev B - smaller, faster, stronger, better looking
2015-09-17 RCA Video
2015-09-20 Widescreen drivers are now in there
2015-09-20 Firmware for widescreen rev B board both Microcontroller and CPLD
